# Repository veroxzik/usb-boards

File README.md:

# usb-boards

A collection of USB boards. Click a subfolder for more information.

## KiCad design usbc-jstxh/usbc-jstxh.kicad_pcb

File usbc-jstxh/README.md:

# USB-C to JST-XH

This is a simple board to convert JST-XH pinout used by the Yuancon controllers to a USB-C socket.  
This board uses a straight JST-XH and a straight USB-C connector.

## Bill of Materials

| Component | Qty | LCSC Part Number |
|:---|:---:|:---:|
| USB-C Connector | 1 | C168704 | 
| JST-XH 4 pin | 1 | C161871 (Official) **OR** C37815 (Knockoff) |
| 5.1kOhm 0805 | 1 | C27834 |

## Dimensions

The board size is 70mm x 20mm. There are two M3 (4-40) holes 60mm apart, centered about the board and about the USB connector.

## Pinout

For the JST-XH:
|Pin # | Signal |
|:---:|:---|
| 1 | +5V |
| 2 | D- |
| 3 | D+ |
| 4 | GND |

This pinout is the mirror of what is on the Yuancon, as the stock cable flips the pinout.

## USB-C

This USB connector only supports USB 2.0. If using a USB-C to USB-C cable, the 5.1kOhm restors **must** be used.  
They can be omitted for USB-A to USB-C cables.

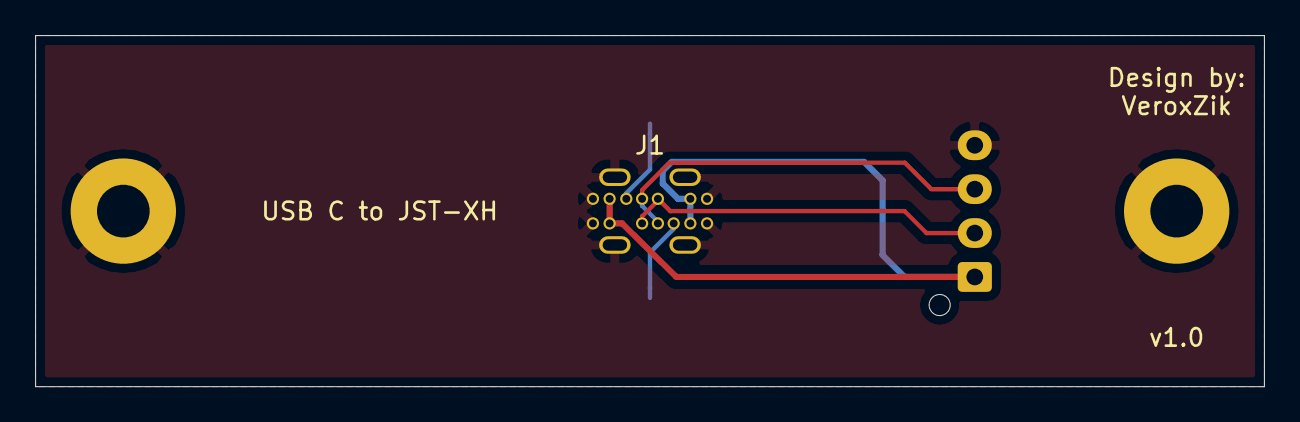
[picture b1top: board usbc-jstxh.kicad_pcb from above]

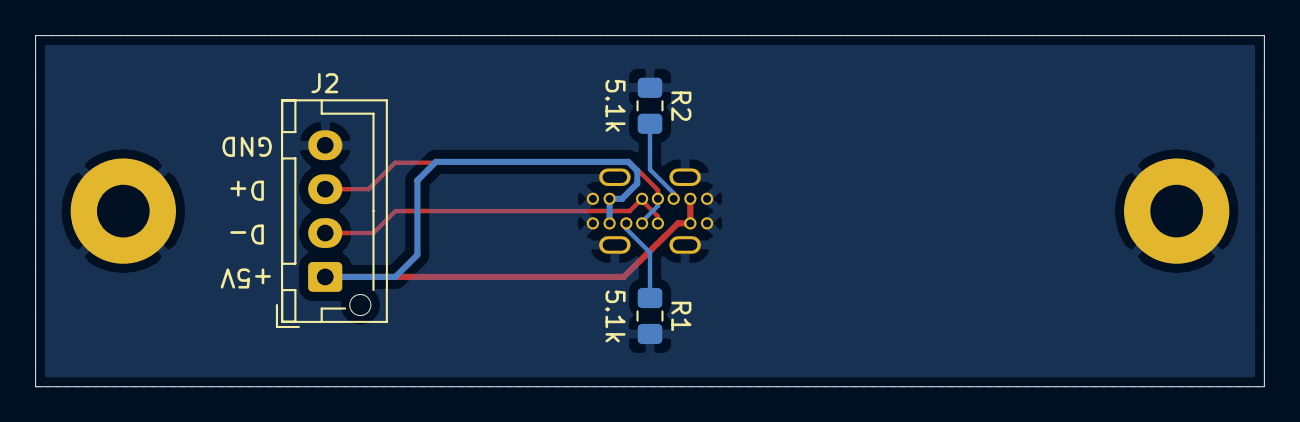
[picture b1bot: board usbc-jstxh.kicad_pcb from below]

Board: 2 copper layers, 70.0 x 20.0 mm, 6 parts (3 on the bottom side), 6 nets.

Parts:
H1, H2: 3mm; MountingHole_3mm_Pad
J1: C168704
J2: Conn_01x04; JST_XH_B4B-XH-AM_1x04_P2.50mm_Vertical
R1, R2: 5.1k; R_0805_2012Metric_Pad1.15x1.40mm_HandSolder

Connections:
GND: H1.1, H2.1, J1.6, J1.S, J2.4, R1.2, R2.2
unnamed: J1.1, J2.2
unnamed: J1.2, J2.3
unnamed: J1.3, R2.1
unnamed: J1.4, R1.1
unnamed: J1.5, J2.1

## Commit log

2021-01-30 Initial commit of USB C to JST XH board
2021-06-05 Add Mini board based on Yuancon USB-C models.
